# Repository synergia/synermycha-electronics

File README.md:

View this project on [CADLAB.io](https://cadlab.io/project/23388). 

# synermycha-electronics

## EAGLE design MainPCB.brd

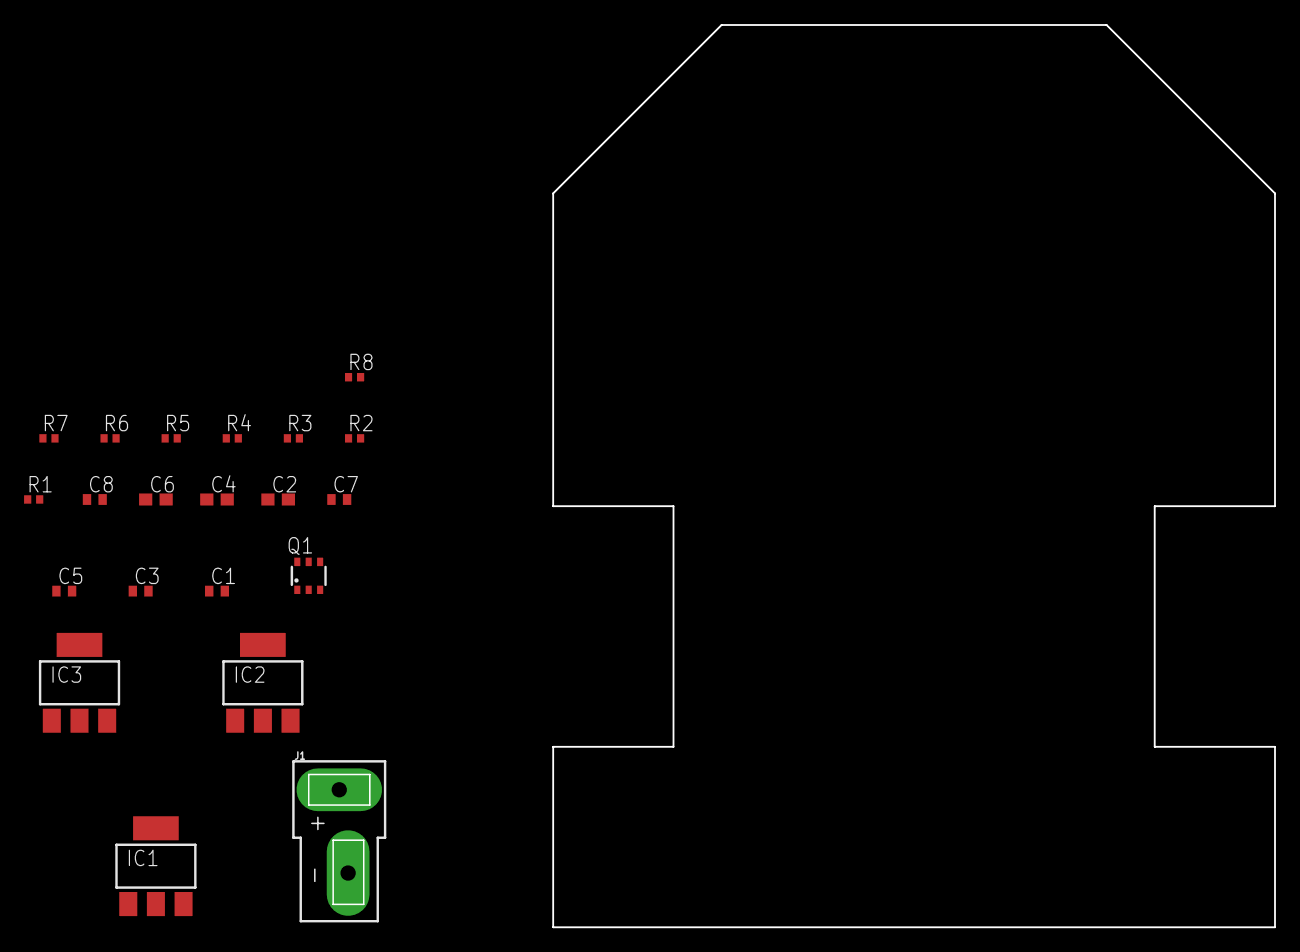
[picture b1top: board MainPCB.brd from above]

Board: 2 copper layers, 80.3 x 75.0 mm, 21 parts (0 on the bottom side), 8 nets, no tracks yet.

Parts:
C1, C3, C5: 0.1uF; C0402
C2, C4, C6: 1uF; C0603
C7: 4.7uF; C0402
C8: 1uF; C0402
IC1, IC2, IC3: LM317MBSTT3; SOT223
J1: DEANS
Q1: SI3481DV; TSOP-6.PAC
R1: 3K3; R0402
R2, R8: 9K1; R0402
R3: 2K2; R0402
R4: 2K7; R0402
R5: 1K2; R0402
R6: 1K8; R0402
R7: 2K4; R0402

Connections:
7V4_UNSAFE: J1.+, Q1.4
+5V: C2.1, C4.1, C6.1, IC1.4, IC2.4, IC3.4, R3.2, R5.2, R7.2
+7V4: C1.1, C3.1, C5.1, C7.1, C8.1, IC1.3, IC2.3, IC3.3, Q1.1, Q1.2, Q1.5, Q1.6, R1.2
BATT_MEAS: R1.1, R2.2
GND: C1.2, C2.2, C3.2, C4.2, C5.2, C6.2, C7.2, C8.2, J1.-, Q1.3, R2.1, R4.1, R6.1, R8.1
unnamed: IC1.1, R3.1, R4.2
unnamed: IC2.1, R5.1, R6.2
unnamed: IC3.1, R7.1, R8.2

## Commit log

2020-03-01 Add gitignore
2020-03-01 Template schematic page
2020-03-01 Voltage sources, schematic division
2020-03-02 Board outline
2020-03-04 Moved to KiCad
2020-03-05 Major upgrade
2020-03-05 Tweaks
    Swapped ENC_L and ENC_R pins, changed UART pins for STM32<->ESP connection, connected buzzer, LCD and IMU I2C lines were splitted and connected accordingly, added I2C pullup resistors
2020-03-06 New footprint for OLED connector
2020-03-06 Power on led
2020-03-06 Many updates
    Added 3V3<->2V8 conversion for VC53L0x and leds for XSHUT of those. PCB update
2020-03-06 uC sch update
2020-03-06 Changed connector for OLED
2020-03-06 Added 2 RGB leds
2020-03-06 Adjusted connections, wiring almost finished
2020-03-06 Adjusted connections in uC schematics
2020-03-06 Renamed vl53l0 project
2020-03-06 Added separate project for encoder boards
2020-03-06 Removed encoders from schematic as moved to the new project
2020-03-06 PWR correction in RGB sch
2020-03-06 Clearing, added 3d model and Synermycha graphics
2020-03-06 Changes in pcb traces names
2020-03-06 Fixed lib and sym-table
2020-03-06 Replaced crystal symbol
2020-03-06 Footprints update, save for cache.lib
2020-03-06 Added gnd via
2020-03-06 Added 3d model for motor mount and hole for mouse eye
2020-03-06 Added led
2020-03-06 Added 5v rail
2020-03-06 Added 2 more RGB leds
2020-03-06 Wired all electronics
2020-03-06 Changes in wiring in main shematic
2020-03-06 Minor tweaks and updates in settings
2020-03-06 Applied changes to PCB
2020-03-06 Added connection to RGB for STM32, remapped some pins
2020-03-07 Minor changes in pinout and layout
2020-03-07 Changes in graphics, tweaks in power input, resistor values
2020-03-07 Minor update in pin connections
    Connected Mouse eye led to PWM output
2020-03-07 Aesthetics update
2020-03-07 Sound emission hole
2020-03-07 Pinout matching with cube_mx
2020-03-07 Pinout matching ctn
2020-03-07 Issues
2020-03-07 Resistor numbers and values
2020-03-07 Applying to PCB
2020-03-08 Changes in graphics, added capacitors, changes in xshut
2020-03-09 Cosmetics update
2020-03-09 Estetics
2020-03-10 Finished encoders, added XSHUT pullups
2020-03-10 Changed location of battery connector
2020-03-10 Flip led, fix path
2020-03-10 Cosmetics
2020-08-28 Odwrócono footprint prawego enkodera
2020-09-28 Czyszczenie
    Usunięto linie 5V oraz 2V8. Poprawiono symbol dla diody RGB
2020-09-28 quick save
2020-09-30 Zmieniono moduł wifi na bluetooth oraz złącze usb - c
2020-09-30 Holy $hi3t
2020-10-02 USB-C PD charging and cell balancing.
2020-10-02 Zmieniono zasilacz +3V3, prowadzenie ścieżek
2020-10-03 Updated BT module connection, 3D models and wiring.
2020-10-03 Encoders update
2020-10-04 Poprawiono ścieżki
2020-10-07 Dodano grafiki do płytek enkodera
2020-10-07 Dodano więcej przelotek do masy
2020-10-07 Estetyka
2020-10-07 Zaktualizowano enkodery
2020-10-07 Aktualizacja enkoderów
2020-10-07 Usunięto rezystor przy buzzerze, poprawiono połączenia do WS2812B
2020-10-08 Backlink to CADLAB.io has been added.
2020-10-24 added new graphics
2020-10-24 Zmiany w drc lepiej oddające możliwości produkcyjne, estetyczne zmiany
2020-10-24 Zmieniono miejsce modelu silników na płytce
2020-10-25 Zmieniono kontroler USB-PD
2020-10-25 Dodano możliwość zasilania (nie tylko ładowania) myszki z usb-c
2020-10-25 Myszka może być wyłączona także podczas zasilania z USB. Zmiany na PCB
2020-10-25 Dodano opis schematu w Power Section
2020-10-25 Kosmetyka
2020-10-25 Podłączono PAD9 U6 do masy
2020-10-26 Pad9 U6 podłączony do GND, poprawki błędów DRC
2020-10-26 Dodano punkty testowe, poprawienie schematu
2020-10-26 Główny schemat jest teraz w portrait mode
2020-10-26 Dodano balancer BQ29209 do biblioteki
2020-10-26 Zmiana balancera na znaną firmę, wyliczenia
2020-10-27 Usunięto ładowanie baterii i usb-c
2020-10-30 Dodano ścieżki łączące STM do USB
2020-10-30 Tuning ścieżek
2020-11-02 Dodano projekt stacji dokującej. Poprawki ścieżek i shcematu
2020-11-03 Zmiany przy składaniu zamówienia
2021-01-15 NXP version
2021-01-15 Back to STM, added level shifter for RGB
2021-02-04 Update DC motor holder model
2021-03-09 Add nrf52805
2022-10-26 Cleanup libraries and port them to KiCad 6 format
2022-10-26 Update files to KiCad6 format
2022-10-26 Remove old files
2022-10-26 Remove obsolete files
2022-10-26 Remove gerbers
2022-10-26 Further cleanup
2022-10-26 Remove encoders gerbers
2022-10-26 Rename wks sheet
2022-10-26 Update gitignore
2022-10-26 Update subsheet names
2022-10-26 Update wks name in project file
2022-10-26 Change naming from SOM to MCU
2022-10-26 Add bus to the motor controller
2022-10-26 Annotate parts, add more buses
2022-10-27 Cleanup bluetooth schematic
2022-10-27 Clean buttons schematic
2022-10-27 Cleanup distance sensors schematic
2022-10-27 Cleanup encoders schematic
2022-10-27 Clear test points
2022-10-27 Change IMU to BNO055
2022-10-27 Cleanup led-oled schematic
2022-10-27 Add more buses
2022-10-27 Update motor driver symbol, cleanup
2022-10-27 Cleanup RGB schematic
2022-10-27 Cleanup power section, start over
2022-10-27 Update root sheet
2022-10-27 Import changes to PCB
2022-11-02 Start power section from scratch
2022-11-02 Add DCDC converters
2022-11-02 Replace buttons with minature joystick
2022-11-02 Autoupdate filed in microcontroller schematic
2022-11-02 Add new components to PCB, DCDC placement, joystick placement
2022-11-03 Add led driving fets
2022-11-03 Add note to the voltages
2022-11-03 Add buzzer, change diode to 1N4xxx
2022-11-03 Pull changes to PCB, update joy footprint
2022-11-03 Update PCB with schematic changes
2022-11-04 Remove VLX wiring
2022-11-04 Add footprint for AS3504 boards
2022-11-04 Update encoder board pads on PCB
2022-11-30 Loclib, cleanup
